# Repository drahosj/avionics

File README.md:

Requires the KiCad libraries from https://github.com/aerodynelabs/kicadlib. Clone that repository into the same directory as this repository.

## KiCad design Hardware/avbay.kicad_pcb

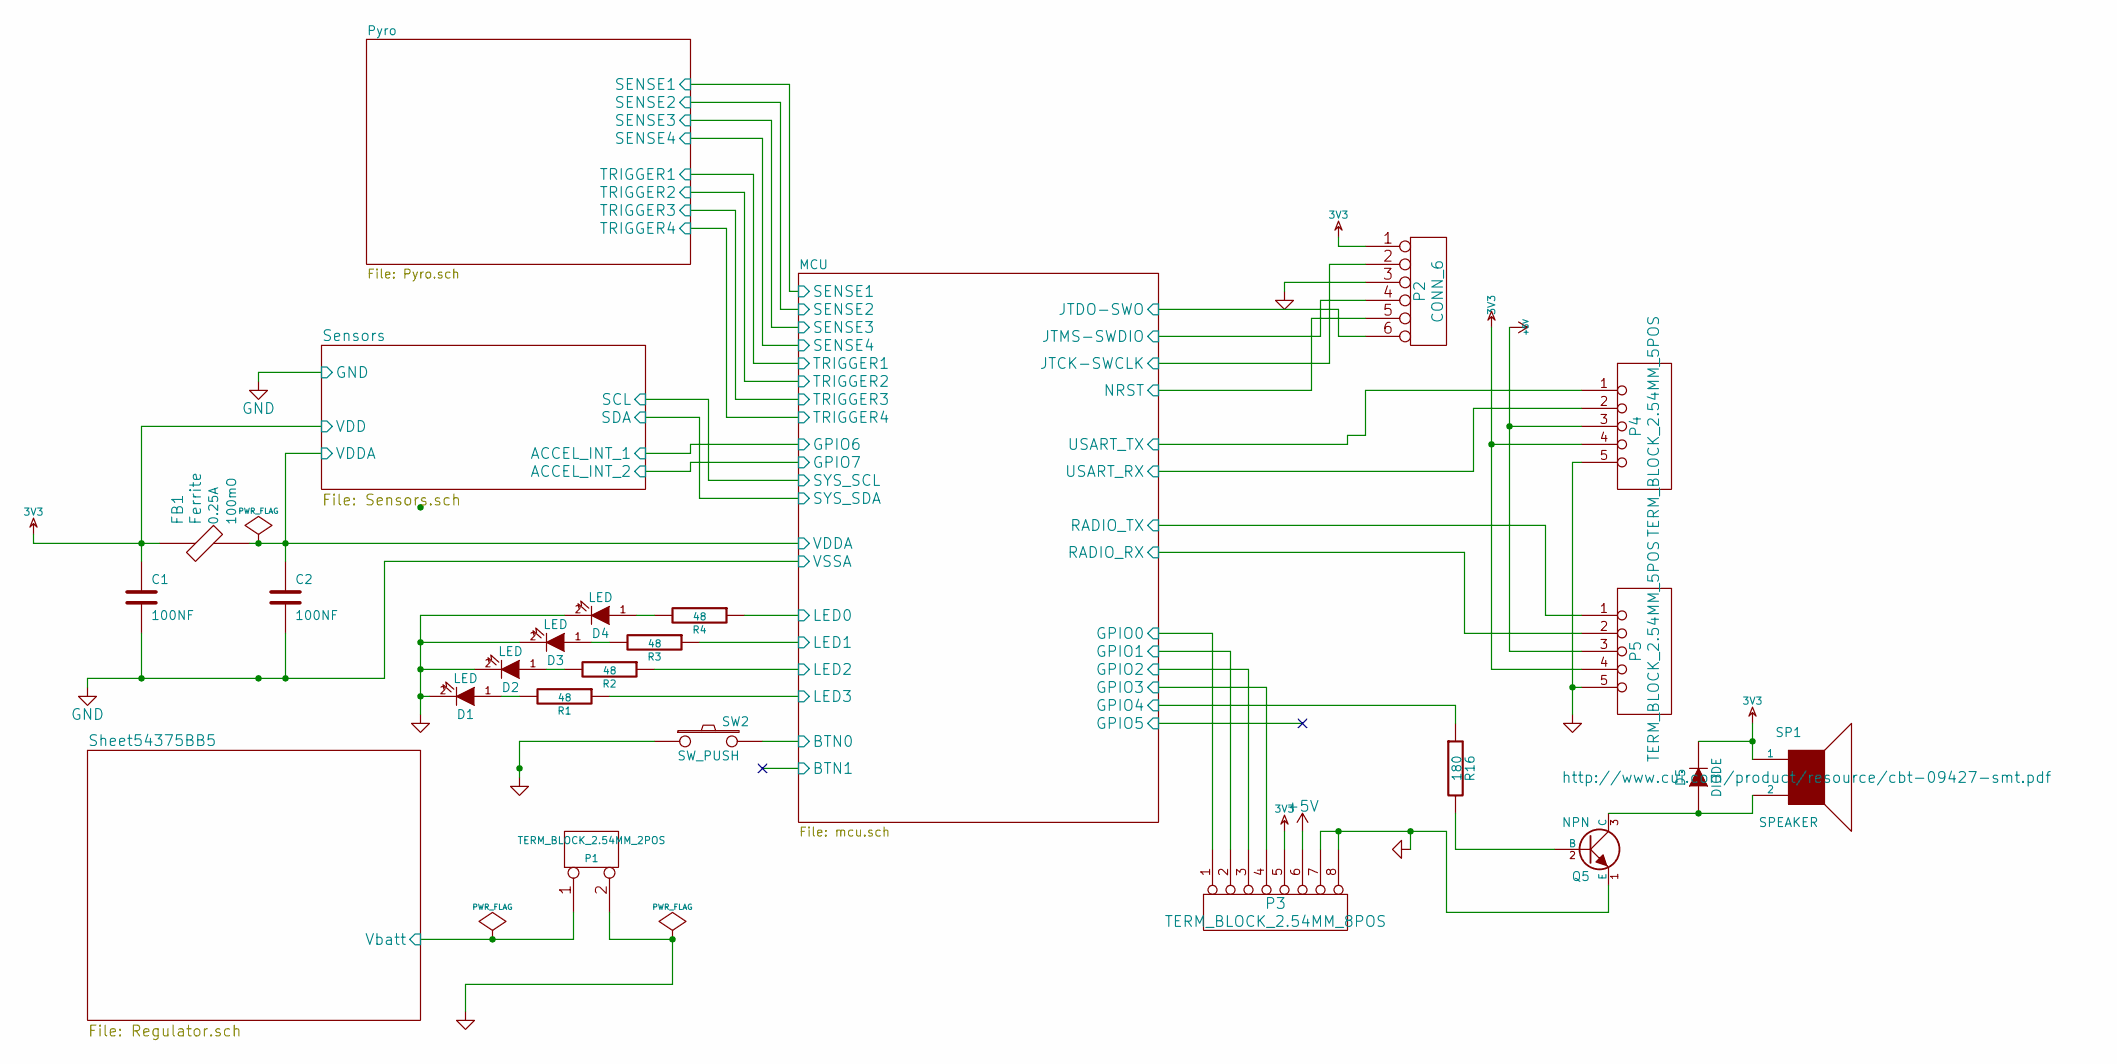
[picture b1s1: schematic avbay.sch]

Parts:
C1, C2: 100NF; C_0805_HandSoldering
D1, D2, D3, D4: LED; LED-0805
D5: DIODE; Diode-MELF_Handsoldering
FB1: Ferrite; SMD-1206; Manufacturer Part # Value
P1: TERM_BLOCK_2.54MM_2POS; TERM_BLOCK_2
P2: CONN_6; Socket_Strip_Straight_1x06
P3: TERM_BLOCK_2.54MM_8POS; Socket_Strip_Straight_1x08
P4, P5: TERM_BLOCK_2.54MM_5POS; TERM_BLOCK_5
Q5: NPN; SOT-23_Handsoldering
R1, R2, R3, R4: 48; R_0805_HandSoldering
R16: 180; R_0805_HandSoldering
SP1: SPEAKER; CBT-07427
SW2: SW_PUSH; SW_SMD

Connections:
3V3: C1.1, D5.2 (K), FB1.1, P2.1, P3.5, P4.4, P5.4, SP1.1; also elsewhere on the board
+5V: P3.6, P4.3, P5.3; also elsewhere on the board
/MCU/BTN0: SW2.2; also elsewhere on the board
/MCU/GPIO0: P3.1; also elsewhere on the board
/MCU/GPIO1: P3.2; also elsewhere on the board
/MCU/GPIO2: P3.3; also elsewhere on the board
/MCU/GPIO3: P3.4; also elsewhere on the board
/MCU/GPIO4: R16.1; also elsewhere on the board
/MCU/JTCK-SWCLK: P2.2; also elsewhere on the board
/MCU/JTDO-SWO: P2.6; also elsewhere on the board
/MCU/JTMS-SWDIO: P2.4; also elsewhere on the board
/MCU/LED0: R4.1; also elsewhere on the board
/MCU/LED1: R3.1; also elsewhere on the board
/MCU/LED2: R2.1; also elsewhere on the board
/MCU/LED3: R1.1; also elsewhere on the board
/MCU/NRST: P2.5; also elsewhere on the board
/MCU/RADIO_RX: P5.2; also elsewhere on the board
/MCU/RADIO_TX: P5.1; also elsewhere on the board
/MCU/USART_RX: P4.2; also elsewhere on the board
/MCU/USART_TX: P4.1; also elsewhere on the board
/MCU/VDDA: C2.1, FB1.2; also elsewhere on the board
/Sheet54375BB5/Vbatt: P1.1; also elsewhere on the board
GND: C1.2, C2.2, D1.2 (K), D2.2 (K), D3.2 (K), D4.2 (K), P1.2 (PM), P2.3, P3.7, P3.8, P4.5, P5.5, Q5.1 (E), SW2.1; also elsewhere on the board
unnamed: D1.1 (A), R1.2
unnamed: D2.1 (A), R2.2
unnamed: D3.1 (A), R3.2
unnamed: D4.1 (A), R4.2
unnamed: D5.1 (A), Q5.3 (C), SP1.2
unnamed: Q5.2 (B), R16.2

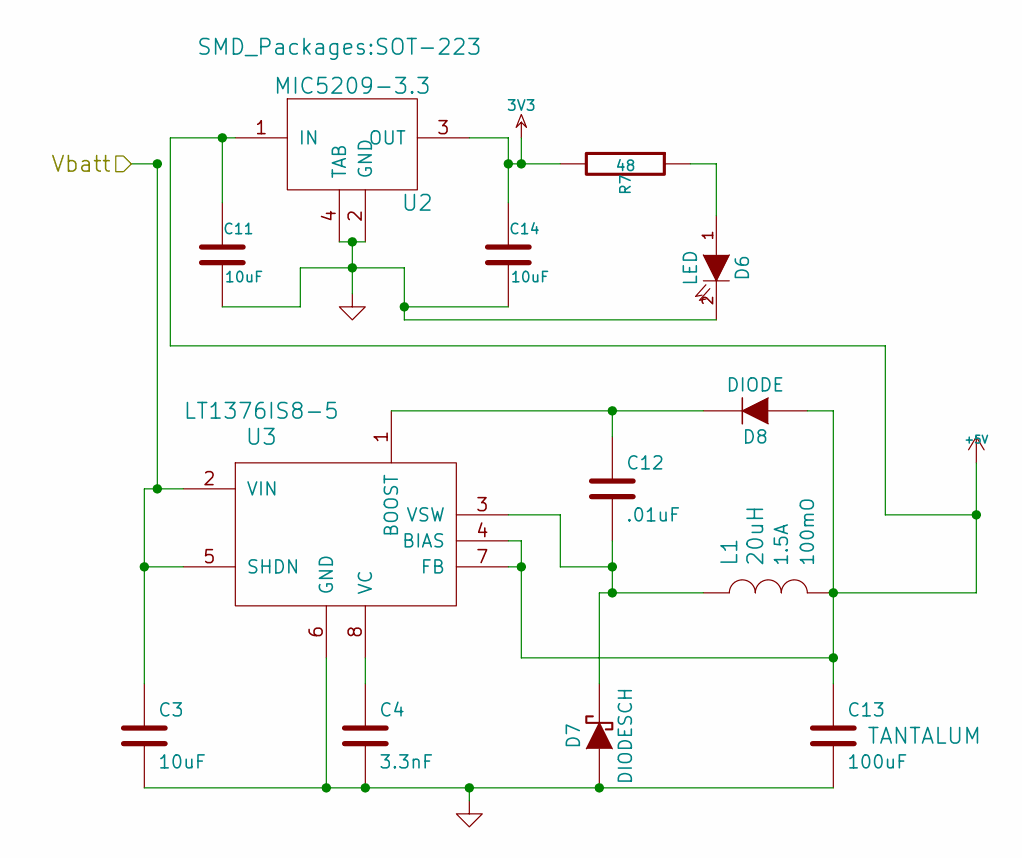
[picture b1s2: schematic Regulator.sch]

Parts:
C3, C11, C14: 10uF; C_0805_HandSoldering
C4: 3.3nF; C_0805_HandSoldering
C12: .01uF; C_0805_HandSoldering
C13: 100uF; TantalC_SizeD_EIA-7343_HandSoldering
D6: LED; LED-0805
D7: DIODESCH; Diode-MELF_Handsoldering
D8: DIODE; Diode-MELF_Handsoldering
L1: 20uH; C_2220_HandSoldering; Manufacturer Part # Value
R7: 48; R_0805_HandSoldering
U2: MIC5209-3.3; SOT-223
U3: LT1376IS8-5; SOIC-8_3.9x4.9mm_Pitch1.27mm

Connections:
3V3: C14.1, R7.2, U2.3 (OUT); also elsewhere on the board
+5V: C11.1, C13.1, D8.1 (A), L1.2, U2.1 (IN), U3.4 (BIAS), U3.7 (FB); also elsewhere on the board
/Sheet54375BB5/Vbatt: C3.1, U3.2 (VIN), U3.5 (SHDN); also elsewhere on the board
GND: C3.2, C4.2, C11.2, C13.2, C14.2, D6.2 (K), D7.1 (A), U2.2 (GND), U2.4 (TAB), U3.6 (GND); also elsewhere on the board
unnamed: C4.1, U3.8 (VC)
unnamed: C12.1, D8.2 (K), U3.1 (BOOST)
unnamed: C12.2, D7.2 (K), L1.1, U3.3 (VSW)
unnamed: D6.1 (A), R7.1

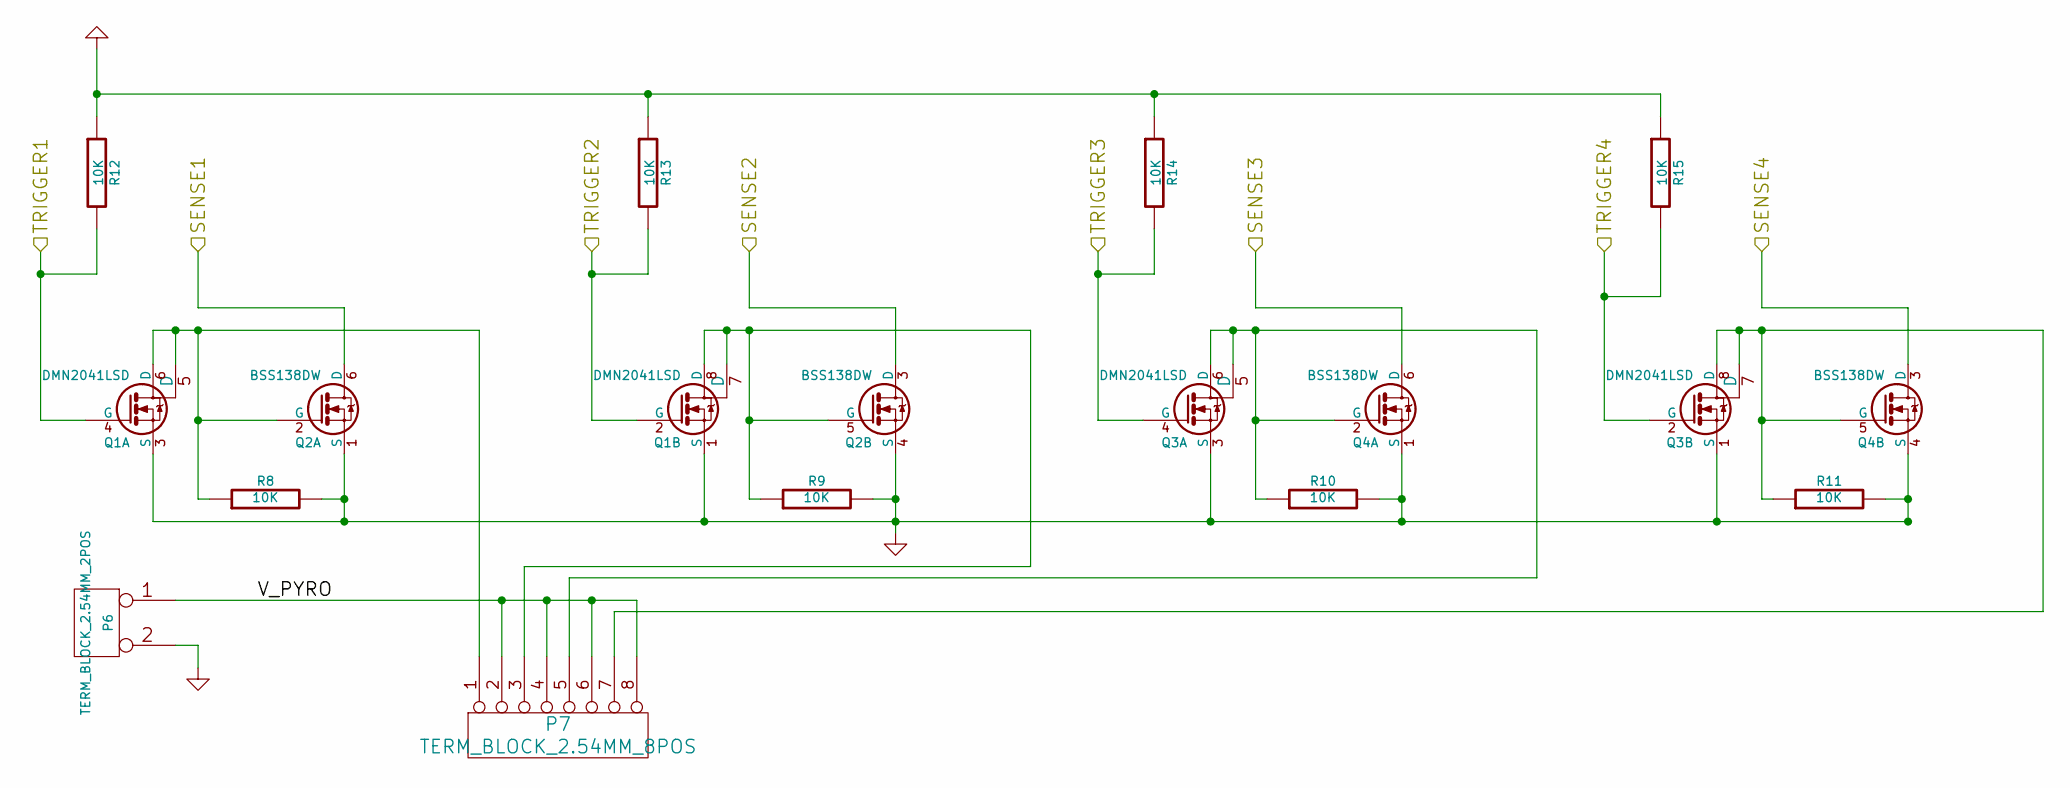
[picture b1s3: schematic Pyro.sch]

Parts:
P6: TERM_BLOCK_2.54MM_2POS; TERM_BLOCK_2
P7: TERM_BLOCK_2.54MM_8POS; TERM_BLOCK_8
Q1, Q3: DMN2041LSD; SOIC-8_3.9x4.9mm_Pitch1.27mm
Q2, Q4: BSS138DW; SC70-6_Handsoldering
R8, R9, R10, R11, R12, R13, R14, R15: 10K; R_0805_HandSoldering

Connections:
/MCU/SENSE1: Q2.6 (D); also elsewhere on the board
/MCU/SENSE2: Q2.3 (D); also elsewhere on the board
/MCU/SENSE3: Q4.6 (D); also elsewhere on the board
/MCU/SENSE4: Q4.3 (D); also elsewhere on the board
/MCU/TRIGGER1: Q1.4 (G), R12.2; also elsewhere on the board
/MCU/TRIGGER2: Q1.2 (G), R13.2; also elsewhere on the board
/MCU/TRIGGER3: Q3.4 (G), R14.2; also elsewhere on the board
/MCU/TRIGGER4: Q3.2 (G), R15.2; also elsewhere on the board
/Pyro/V_PYRO: P6.1, P7.2, P7.4, P7.6, P7.8
GND: P6.2 (PM), Q1.1 (S), Q1.3 (S), Q2.1 (S), Q2.4 (S), Q3.1 (S), Q3.3 (S), Q4.1 (S), Q4.4 (S), R8.2, R9.2, R10.2, R11.2, R12.1, R13.1, R14.1, R15.1; also elsewhere on the board
unnamed: P7.1, Q1.5 (D), Q1.6 (D), Q2.2 (G), R8.1
unnamed: P7.3, Q1.7 (D), Q1.8 (D), Q2.5 (G), R9.1
unnamed: P7.5, Q3.5 (D), Q3.6 (D), Q4.2 (G), R10.1
unnamed: P7.7, Q3.7 (D), Q3.8 (D), Q4.5 (G), R11.1

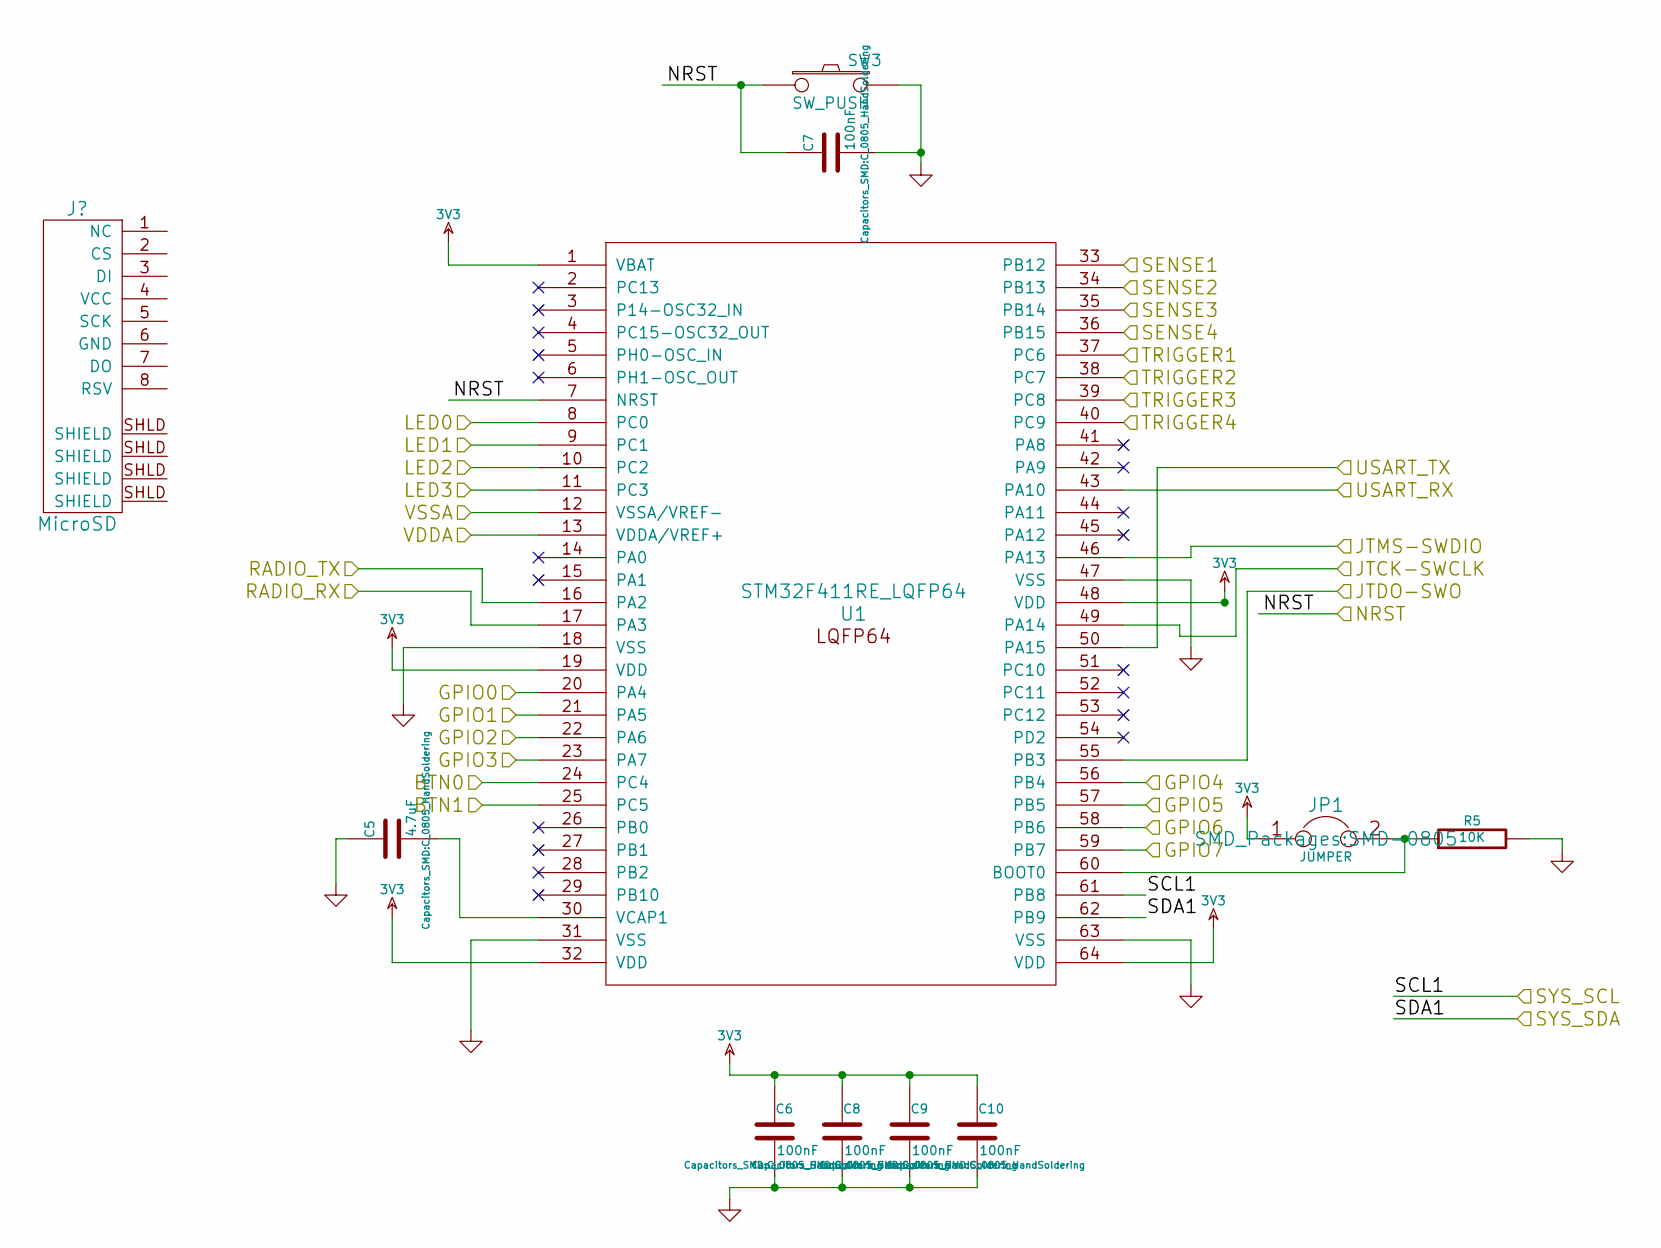
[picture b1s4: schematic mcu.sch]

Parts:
C5: 4.7uF; C_0805_HandSoldering
C6, C7, C8, C9, C10: 100nF; C_0805_HandSoldering
JP1: JUMPER; SMD-0805
R5: 10K; R_0805_HandSoldering
SW3: SW_PUSH; SW_SMD_MICRO
U1: STM32F411RE_LQFP64; TQFP-64_10x10mm_Pitch0.5mm

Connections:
3V3: C6.1, C8.1, C9.1, C10.1, JP1.1, U1.1 (VBAT), U1.19 (VDD), U1.32 (VDD), U1.48 (VDD), U1.64 (VDD); also elsewhere on the board
/MCU/BTN0: U1.24 (PC4); also elsewhere on the board
/MCU/BTN1: U1.25 (PC5)
/MCU/GPIO0: U1.20 (PA4); also elsewhere on the board
/MCU/GPIO1: U1.21 (PA5); also elsewhere on the board
/MCU/GPIO2: U1.22 (PA6); also elsewhere on the board
/MCU/GPIO3: U1.23 (PA7); also elsewhere on the board
/MCU/GPIO4: U1.56 (PB4); also elsewhere on the board
/MCU/GPIO5: U1.57 (PB5)
/MCU/JTCK-SWCLK: U1.49 (PA14); also elsewhere on the board
/MCU/JTDO-SWO: U1.55 (PB3); also elsewhere on the board
/MCU/JTMS-SWDIO: U1.46 (PA13); also elsewhere on the board
/MCU/LED0: U1.8 (PC0); also elsewhere on the board
/MCU/LED1: U1.9 (PC1); also elsewhere on the board
/MCU/LED2: U1.10 (PC2); also elsewhere on the board
/MCU/LED3: U1.11 (PC3); also elsewhere on the board
/MCU/NRST: C7.1, SW3.1, U1.7 (NRST); also elsewhere on the board
/MCU/RADIO_RX: U1.17 (PA3); also elsewhere on the board
/MCU/RADIO_TX: U1.16 (PA2); also elsewhere on the board
/MCU/SENSE1: U1.33 (PB12); also elsewhere on the board
/MCU/SENSE2: U1.34 (PB13); also elsewhere on the board
/MCU/SENSE3: U1.35 (PB14); also elsewhere on the board
/MCU/SENSE4: U1.36 (PB15); also elsewhere on the board
/MCU/TRIGGER1: U1.37 (PC6); also elsewhere on the board
/MCU/TRIGGER2: U1.38 (PC7); also elsewhere on the board
/MCU/TRIGGER3: U1.39 (PC8); also elsewhere on the board
/MCU/TRIGGER4: U1.40 (PC9); also elsewhere on the board
/MCU/USART_RX: U1.43 (PA10); also elsewhere on the board
/MCU/USART_TX: U1.50 (PA15); also elsewhere on the board
/MCU/VDDA: U1.13 (VDDA/VREF+); also elsewhere on the board
/Sensors/ACCEL_INT_1: U1.58 (PB6); also elsewhere on the board
/Sensors/ACCEL_INT_2: U1.59 (PB7); also elsewhere on the board
/Sensors/SCL: U1.61 (PB8); also elsewhere on the board
/Sensors/SDA: U1.62 (PB9); also elsewhere on the board
GND: C5.1, C6.2, C7.2, C8.2, C9.2, C10.2, R5.2, SW3.2, U1.12 (VSSA/VREF-), U1.18 (VSS), U1.31 (VSS), U1.47 (VSS), U1.63 (VSS); also elsewhere on the board
unnamed: C5.2, U1.30 (VCAP1)
unnamed: JP1.2, R5.1, U1.60 (BOOT0)

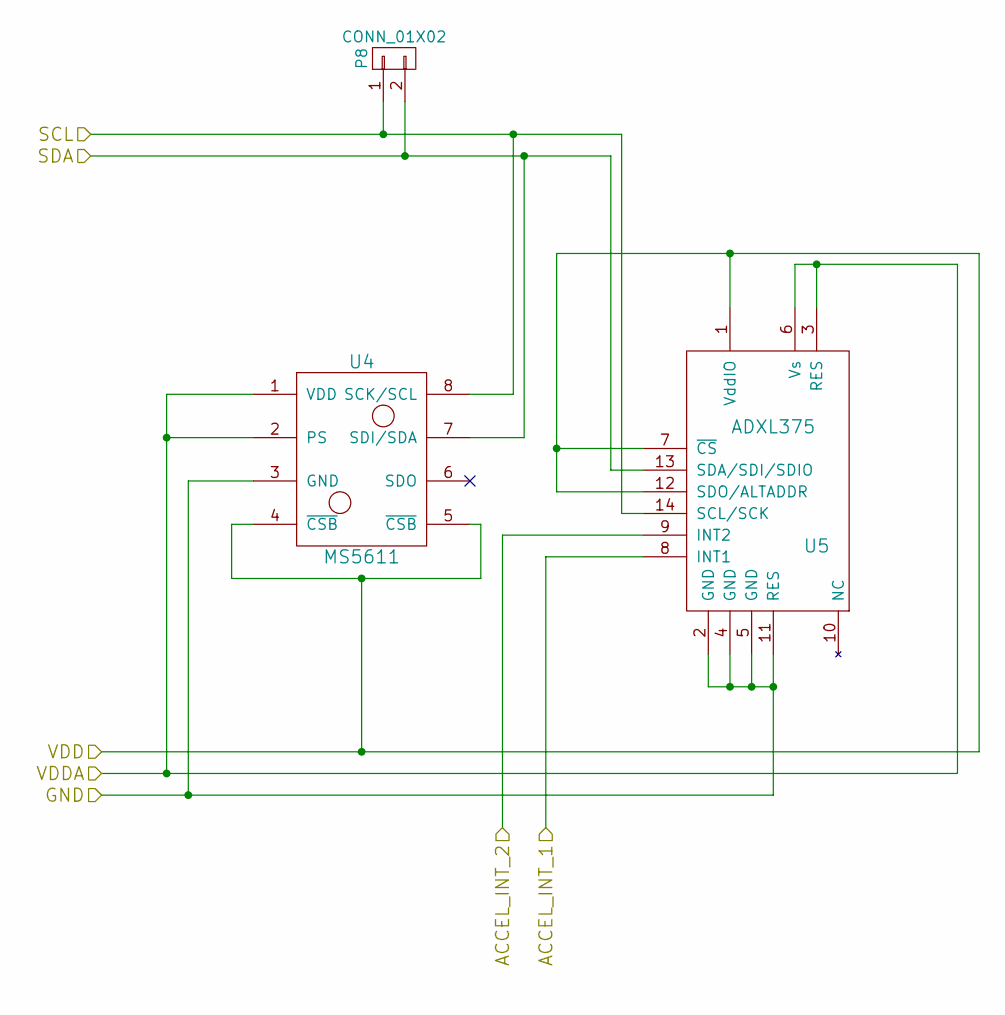
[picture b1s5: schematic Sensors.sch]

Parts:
P8: CONN_01X02; Socket_Strip_Straight_2x01
U4: MS5611; MS5611-EXT
U5: ADXL375; ADXL375-EXT

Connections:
3V3: U4.4 (~CSB), U4.5 (~CSB), U5.1 (VddIO), U5.7 (~CS), U5.12 (SDO/ALTADDR); also elsewhere on the board
/MCU/VDDA: U4.1 (VDD), U4.2 (PS), U5.3 (RES), U5.6 (Vs); also elsewhere on the board
/Sensors/ACCEL_INT_1: U5.8 (INT1); also elsewhere on the board
/Sensors/ACCEL_INT_2: U5.9 (INT2); also elsewhere on the board
/Sensors/SCL: P8.1, U4.8 (SCK/SCL), U5.14 (SCL/SCK); also elsewhere on the board
/Sensors/SDA: P8.2, U4.7 (SDI/SDA), U5.13 (SDA/SDI/SDIO); also elsewhere on the board
GND: U4.3 (GND), U5.2 (GND), U5.4 (GND), U5.5 (GND), U5.11 (RES); also elsewhere on the board

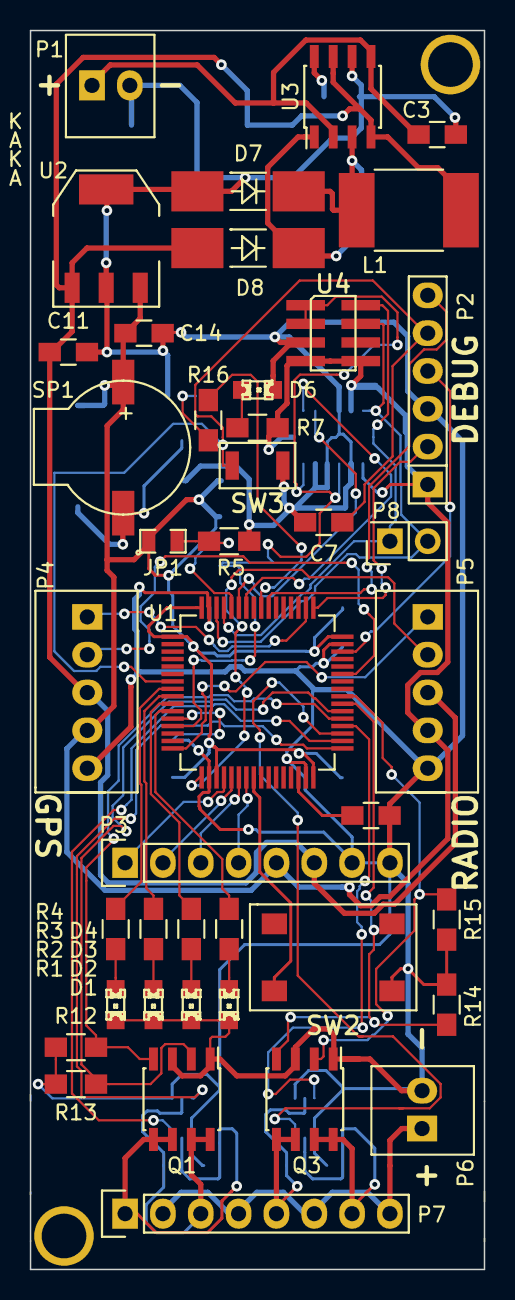
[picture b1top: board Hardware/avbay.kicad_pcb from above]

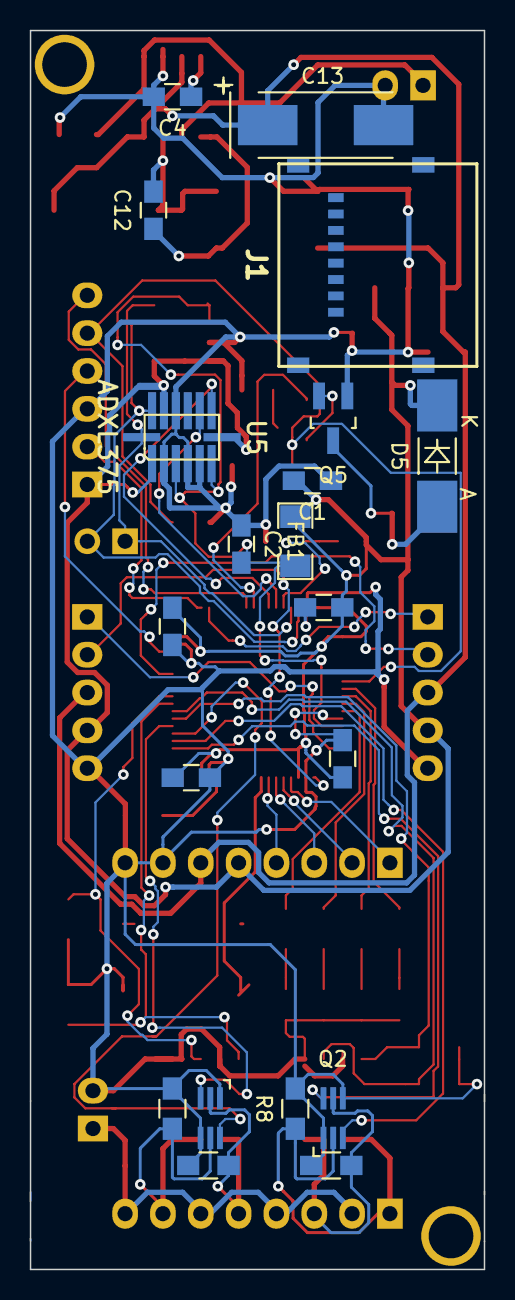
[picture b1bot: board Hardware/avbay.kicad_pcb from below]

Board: 2 copper layers, 30.5 x 83.2 mm, 62 parts (20 on the bottom side), 52 nets.

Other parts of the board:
J1: MicroSD; MICRO_SD_HINGE_AMP

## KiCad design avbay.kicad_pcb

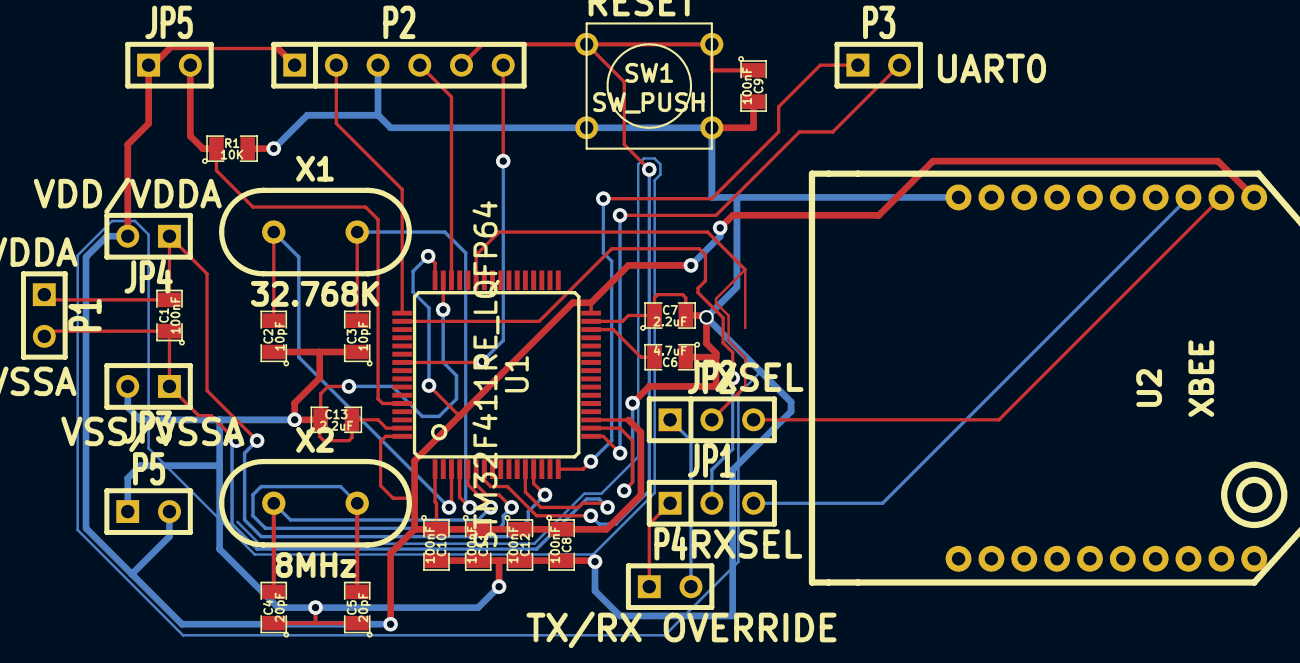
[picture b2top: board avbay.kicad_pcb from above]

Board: 2 copper layers, 29 parts (0 on the bottom side), 22 nets.

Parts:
C1, C8, C9, C10, C11, C12: 100nF; SM0805
C2, C3: 10pF; SM0805
C4, C5: 20pF; SM0805
C6: 4.7uF; SM0805
C7, C13: 2.2uF; SM0805
JP1, JP2: JUMPER3; SIL-3
JP3, JP4, JP5: JUMPER; SIL-2
P1, P3, P4, P5: CONN_2; SIL-2
P2: CONN_6; SIL-6
R1: 10K; SM0805
SW1: SW_PUSH; SW_PUSH_SMALL
U1: STM32F411RE_LQFP64; LQFP64
U2: XBEE; XBee-pro
X1: 32.768K; HC-49V
X2: 8MHz; HC-49V

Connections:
3V3: C8.1, C10.1, C11.1, C12.1, JP4.2, JP5.1, P2.1, P5.2, U1.1, U1.19, U1.32, U1.48, U1.64, U2.1
/MCU/JTCK-SWCLK: P2.2, U1.49
/MCU/JTDO-SWO: P2.6, U1.55
/MCU/JTMS-SWDIO: P2.4, U1.46
/MCU/NRST: C9.1, P2.5, SW1.1, U1.7
/MCU/RADIO_RX: JP2.2, U1.43
/MCU/RADIO_TX: JP1.2, U1.50
/MCU/USART_RX: P3.2, U1.17
/MCU/USART_TX: P3.1, U1.16
/MCU/VDDA: C1.2, JP4.1, P1.1, U1.13
/MCU/VSSA: C1.1, JP3.1, P1.2, U1.12
/OVERRIDE_RX: JP2.1, P4.2
/OVERRIDE_TX: JP1.1, P4.1
/XBEE_RX: JP1.3, U2.3
/XBEE_TX: JP2.3, U2.2
GND: C2.1, C3.1, C4.1, C5.1, C6.1, C7.1, C7.2, C8.2, C9.2, C10.2, C11.2, C12.2, C13.1, C13.2, JP3.2, P2.3, P5.1, R1.2, SW1.2, U1.18, U1.31, U1.47, U1.63, U2.10
unnamed: C5.2, U1.6, X2.2
unnamed: C4.2, U1.5, X2.1
unnamed: C3.2, U1.4, X1.2
unnamed: C2.2, U1.3, X1.1
unnamed: JP5.2, R1.1, U1.60
unnamed: C6.2, U1.30

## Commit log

2014-10-02 Added xbee libraries and modules.
    Added xbee to schematic
2014-10-02 Associated footprints
2014-10-03 Basic PCB routed
    Good starting point for adding stuff
2014-10-05 Prototype made
2014-10-08 Placed and routed basic PCB
    Gonna end up throwing the whole thing out.
    Needs to have GPIO headers added because reasons.
2014-10-11 Added voltage regulators
2014-10-20 Began layout of board
2014-10-21 Changed stuff
    Layed out board with regulators, leds, and GPIOs
2014-11-02 Made breakout board
2014-12-04 Added pyro schematic
2014-12-05 Added pyro circuits
2014-12-05 Began laying out PCB
2014-12-05 Began layout
2014-12-06 New MOSFETs
2014-12-11 Improved schematic
2015-01-24 Added sensors and sensor passives
2015-01-25 Roughed out PCB layout
    Known issues:
    - SW_PUSH holes too small. New footprint needed
    - Sensor footprints are completely wrong.
    - Regulator footprints might not be correct.
    Tasks:
    - Place passives according to schematic (especially
2015-01-29 Tried to add footprints but they don't exist
2015-01-30 Began routing
2015-01-30 Finished routing.
    Board awaiting review
2015-01-30 Remade PDF
2015-03-14 Fixed footprints for tecminal blocks
2015-03-15 Finished schematic work. Began footprints
    Began assigning footprints for R2
2015-03-15 Finished creating footprints
2015-03-15 Ready to begin laying out and routing
2015-06-26 Routed more stuff
    Almost all routing is done, except for the accelerometer interrupt lines
2015-06-26 Fixed a via that was dumb
2015-06-26 Added datasheet reference to buzzer
2015-06-26 Plotted new PDFs and tweaked gitignore
2015-06-27 Switched to tantalum capacitor for power supply
2015-06-27 Added MicroSD card
2015-06-27 Fixed routing
2015-06-27 Front silkscreen
